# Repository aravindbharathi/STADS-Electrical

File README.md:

# STADS Electrical Repository
> Former Branch
This repository contains all the codes that was intended to be used on hardware designed and developed by the team. This design has now evolved and migrated to [AJIT](https://github.com/Student-Satellite-IITM/AJIT-STADS) were the most recent codes are stored. The codes written during the development of the previous design of the Star Tracker, including Verilog, Embedded C, C for HLS and bitstreams to program FPGAs can be found here.

This repository does not include codes for [in-loop simulation](https://github.com/Student-Satellite-IITB/STADS) of the Star Tracker.

## Organization of codes
1. Codes are to be hosted in their respective directories following the file nomenclature as explained in the [QA Guidelines](https://docs.google.com/document/d/1U63RPCxErLuVvC3BmJ-6Fqa9EqF_KslVQfur7OiazCk/edit).
2. Appropriate version control practices are to be followed as mentioned in the QA Guidelines.
3. Any arguments to be fed into C codes are to be given as arguments to `main()` and run from the command line. The `main()` should look as follows:
```
int main(int argc, char** argv)
{
    \\ insert main code here
}
```
4. Do not include any non-code / non-bitstream files (such as .txt, .jpg, .png, etc.) in the repository unless they are absolutely necessary.

<!--## Structure of the Repository-->

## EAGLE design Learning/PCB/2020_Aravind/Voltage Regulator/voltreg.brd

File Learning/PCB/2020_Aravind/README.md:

# PCB Learning Task Documentation

[Original Google Doc](https://docs.google.com/document/d/1QxEvF37-TI_voJEB7cvCeUME1jytATv3Iuk63UNRfNU/edit)

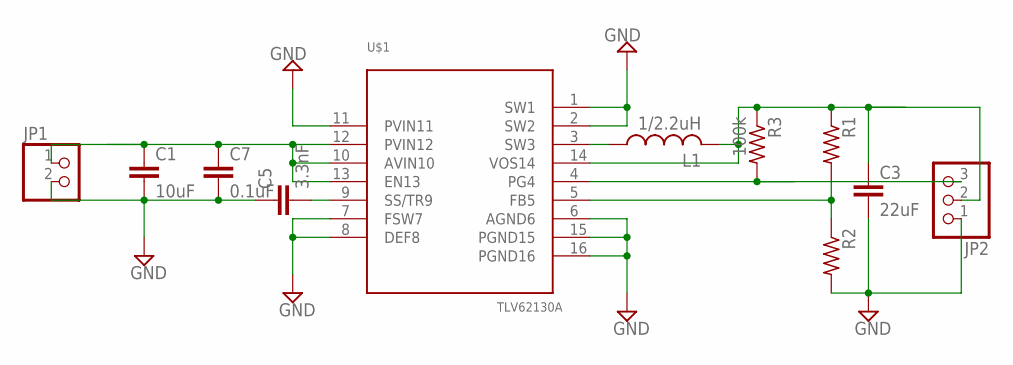
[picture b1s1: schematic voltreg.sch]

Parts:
C1: 10uF; C0805
C3: 22uF; C0805
C5: 3.3nF; C0805
C7: 0.1uF; C0805
JP1: PINHD-1X2; 1X02
JP2: PINHD-1X3; 1X03
L1: 1/2.2uH; L3225M
R1, R2: R-US_R0805; R0805
R3: 100k; R0805
U$1: TLV62130A

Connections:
GND: C1.2, C3.2, C5.1, C7.2, JP1.2, JP2.1, R2.2, U$1.1 (SW1), U$1.2 (SW2), U$1.6 (AGND6), U$1.7 (FSW7), U$1.8 (DEF8), U$1.11 (PVIN11), U$1.15 (PGND15), U$1.16 (PGND16)
unnamed: L1.1, U$1.3 (SW3)
unnamed: C3.1, JP2.2, L1.2, R1.1, R3.1, U$1.14 (VOS14)
unnamed: JP2.3, R3.2, U$1.4 (PG4)
unnamed: R1.2, R2.1, U$1.5 (FB5)
unnamed: C1.1, C7.1, JP1.1, U$1.10 (AVIN10), U$1.12 (PVIN12), U$1.13 (EN13)
unnamed: C5.2, U$1.9 (SS/TR9)

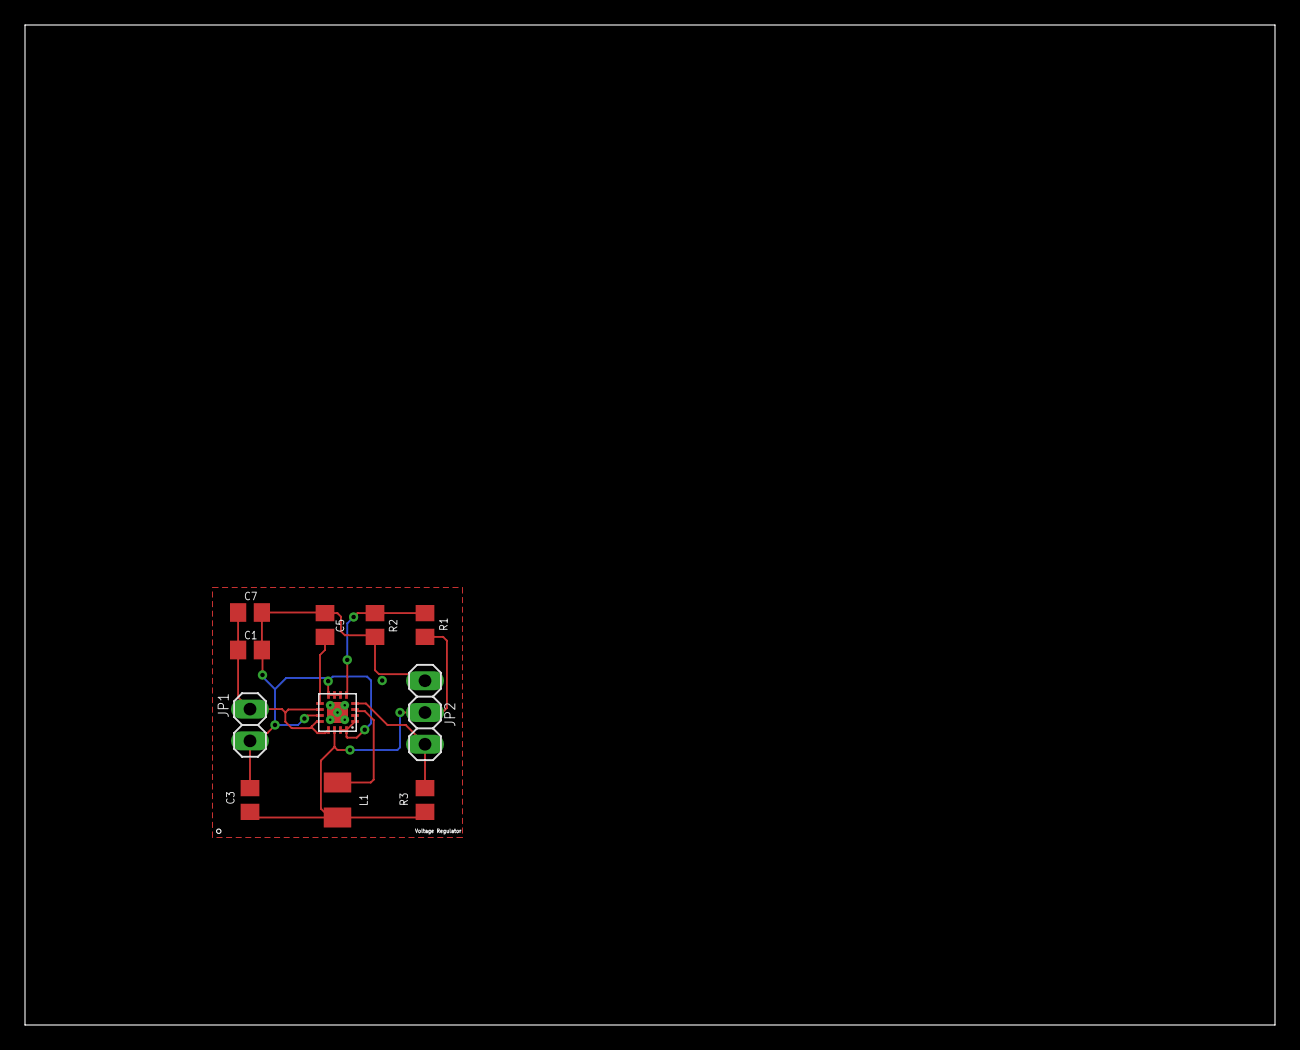
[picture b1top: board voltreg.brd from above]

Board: 2 copper layers, 100.0 x 80.0 mm, 11 parts (0 on the bottom side), 7 nets.

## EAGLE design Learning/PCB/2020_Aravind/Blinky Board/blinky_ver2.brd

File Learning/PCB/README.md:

# PCB Learning Tasks

### Basics:
1. [Link](https://www.autodesk.in/products/eagle/free-download) to download EAGLE
2. [Tutorial Series for EAGLE](https://youtube.com/playlist?list=PL868B73617C6F6FAD) to get started. Implement the Blinky Board alongside. Do not passively watch the videos.
3. Understand and implement the Voltage Regulator as described in [this datasheet](2020_Aravind/Voltage%20Regulator/Voltage%20Regulator%20Datasheet)
4. [BGA Fanout](https://www.youtube.com/watch?v=XgJomyAvxrA)
5. [QA Guidelines PCB](https://docs.google.com/document/d/1JELd9mMEQRspMHAz204R0znwcZccqAV9WsKYcaW38Cc/edit#heading=h.nrnw03t7conb)

### Advanced:
- [Multilayer boards](2021_Durgaprasad)

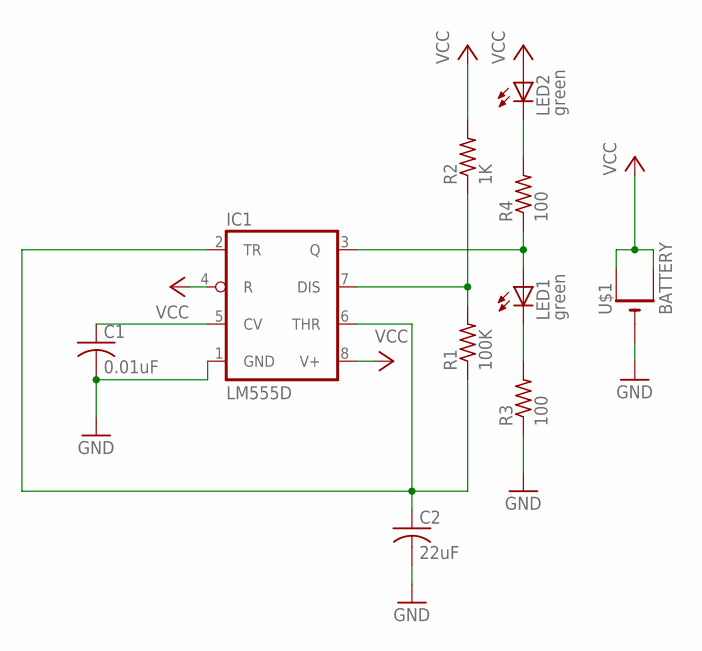
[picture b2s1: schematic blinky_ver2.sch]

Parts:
C1: 0.01uF; C0805
C2: 22uF; C0805
IC1: LM555D; SO08
LED1, LED2: green; CHIPLED_0805
R1: 100K; R0805
R2: 1K; R0805
R3, R4: 100; R0805
U$1: BATTERY; CR1220-SMD

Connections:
GND: C1.2, C2.2, IC1.1 (GND), R3.1, U$1.-
unnamed: LED2.C, R4.2
unnamed: IC1.3 (Q), LED1.A, R4.1
unnamed: LED1.C, R3.2
unnamed: IC1.7 (DIS), R1.2, R2.1
unnamed: C1.1, IC1.5 (CV)
unnamed: C2.1, IC1.2 (TR), IC1.6 (THR), R1.1
VCC: IC1.4 (R), IC1.8 (V+), LED2.A, R2.2, U$1.+$1 (+), U$1.+$2 (+1)

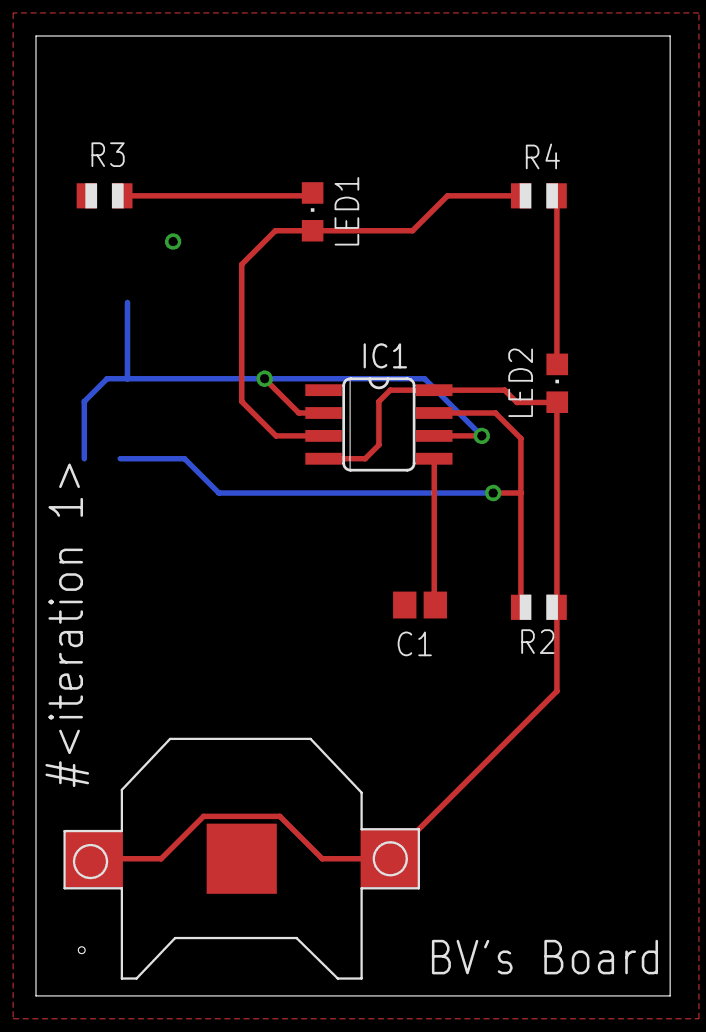
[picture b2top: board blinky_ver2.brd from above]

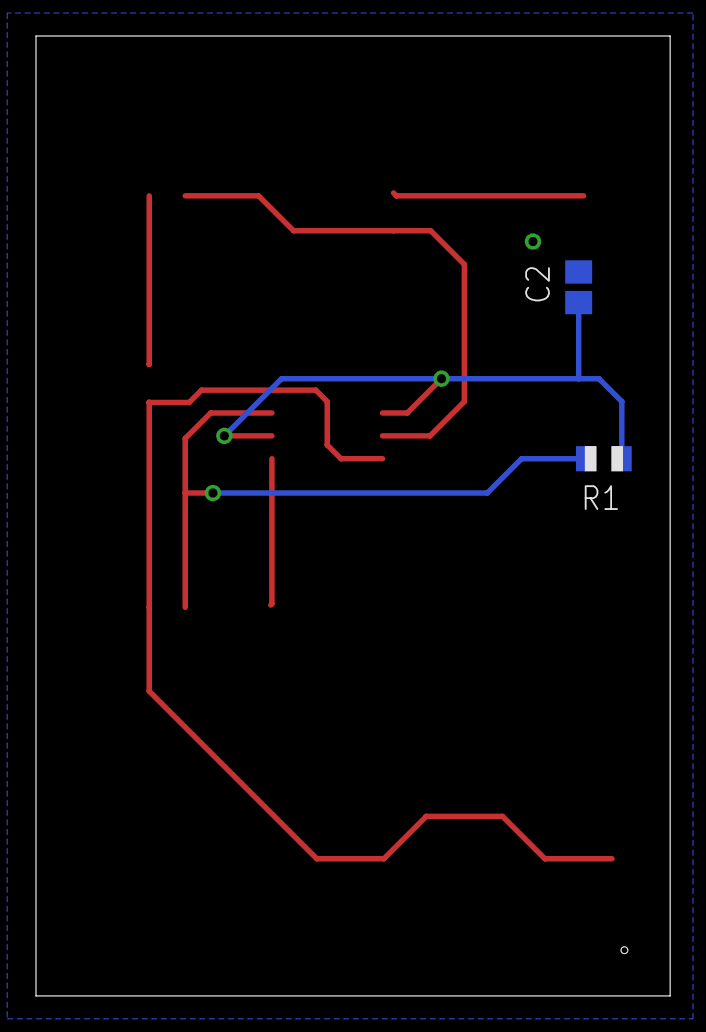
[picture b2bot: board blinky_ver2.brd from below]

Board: 2 copper layers, 35.2 x 53.3 mm, 10 parts (2 on the bottom side), 8 nets.

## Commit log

2021-08-14 Updated Repository Structure and READMEs
2021-08-21 Removed Learning Directory
2021-08-21 Added AJIT repository
2021-08-21 Opened new branch
2021-08-21 Updating README. Checking hyperlinks
2021-08-21 Testing Hyperlinks
2021-08-21 Changed enumeration
2021-08-21 Updated Learning README
2021-08-21 Updated README in Learning and subdirectories
2021-08-21 Updated PCB learning Documentation
2021-08-21 Further updates in PCB Learning Tasks
2021-08-21 Added all learning material for PCB
2021-08-21 Updated READMEs and uploaded learning task miniprojects
2021-08-21 Updated READMEs
2021-08-21 Updated AJIT README
2021-08-21 Deleting Branch
2021-08-21 Retracting changes to structure of repo
